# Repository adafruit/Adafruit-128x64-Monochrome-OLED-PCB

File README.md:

## Adafruit 128x64 Monochrome OLED PCB
<a href="http://www.adafruit.com/products/326"><br/>
<a href="http://www.adafruit.com/products/326"><br/>
Click here to purchase one from the Adafruit shop</a>

These displays are small, only about 1" diagonal, but very readable due to the high contrast of an OLED display. This display is made of 128x64 individual white OLED pixels, each one is turned on or off by the controller chip. Because the display makes its own light, no backlight is required. This reduces the power required to run the OLED and is why the display has such high contrast; we really like this miniature display for its crispness!

This breakout can be used with either an SPI or I2C interface - selectable by soldering two jumpers on the back. The design is completely 5V-ready, with an onboard regulator and built in boost converter. It's easier than ever to connect directly to your 3V or 5V microcontroller without needing any kind of level shifter!

This is the PCB for the Adafruit 128x64 I2C/SPI/Parallel OLED breakout board. The format is EagleCAD schematic and board layout
- http://www.adafruit.com/products/326

### License

Adafruit invests time and resources providing this open source design, please support Adafruit and open-source hardware by purchasing products from [Adafruit](https://www.adafruit.com)!

All text above must be included in any redistribution

Designed by Limor Fried/Ladyada for Adafruit Industries.
Creative Commons Attribution/Share-Alike, all text above must be included in any redistribution. 
See license.txt for additional information.

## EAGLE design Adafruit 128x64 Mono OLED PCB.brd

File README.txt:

This is the PCB for the Adafruit 128x64 I2C/SPI/Parallel OLED breakout board
Format is EagleCAD schematic and board layout

For more details, check out the product page at

-----> http://www.adafruit.com/products/326

Adafruit invests time and resources providing this open source design, 
please support Adafruit and open-source hardware by purchasing 
products from Adafruit!

Designed by Adafruit Industries.  
Creative Commons Attribution, Share-Alike license, check license.txt for more information
All text above must be included in any redistribution

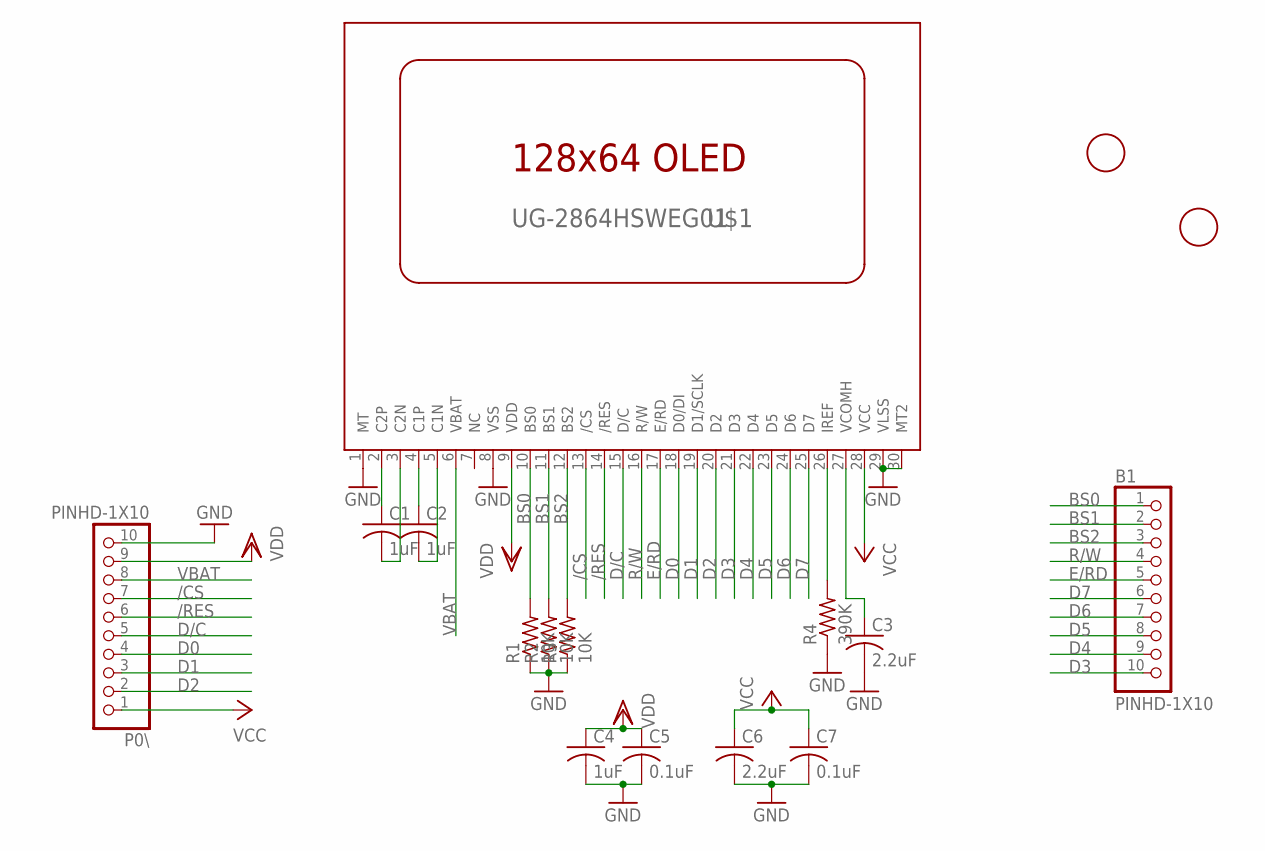
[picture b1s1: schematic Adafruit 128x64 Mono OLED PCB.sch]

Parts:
B1: PINHD-1X10; 1X10-BIG
C1, C2, C4: 1uF; C0805K
C3, C6: 2.2uF; C0805K
C5, C7: 0.1uF; C0805K
P0\: PINHD-1X10; 1X10-BIG
R1, R2, R3: 10K; R0805
R4: 390K; R0805
U$1: UG-2864HSWEG01; 1X30-0.7MM
U$3, U$4: FIDUCIAL; FIDUCIAL_1MM

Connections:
/CS: P0\.7, U$1.13 (/CS)
/RES: P0\.6, U$1.14 (/RES)
BS0: B1.1, R1.2, U$1.10 (BS0)
BS1: B1.2, R2.2, U$1.11 (BS1)
BS2: B1.3, R3.2, U$1.12 (BS2)
D0: P0\.4, U$1.18 (D0/DI)
D1: P0\.3, U$1.19 (D1/SCLK)
D2: P0\.2, U$1.20 (D2)
D3: B1.10, U$1.21 (D3)
D4: B1.9, U$1.22 (D4)
D5: B1.8, U$1.23 (D5)
D6: B1.7, U$1.24 (D6)
D7: B1.6, U$1.25 (D7)
D/C: P0\.5, U$1.15 (D/C)
E/RD: B1.5, U$1.17 (E/RD)
GND: C3.2, C4.2, C5.2, C6.2, C7.2, P0\.10, R1.1, R2.1, R3.1, R4.1, U$1.1 (MT), U$1.8 (VSS), U$1.29 (VLSS), U$1.30 (MT2)
unnamed: C1.2, U$1.3 (C2N)
unnamed: C1.1, U$1.2 (C2P)
unnamed: C2.1, U$1.4 (C1P)
unnamed: C2.2, U$1.5 (C1N)
unnamed: R4.2, U$1.26 (IREF)
unnamed: C3.1, U$1.27 (VCOMH)
R/W: B1.4, U$1.16 (R/W)
VBAT: P0\.8, U$1.6 (VBAT)
VCC: C6.1, C7.1, P0\.1, U$1.28 (VCC)
VDD: C4.1, C5.1, P0\.9, U$1.9 (VDD)

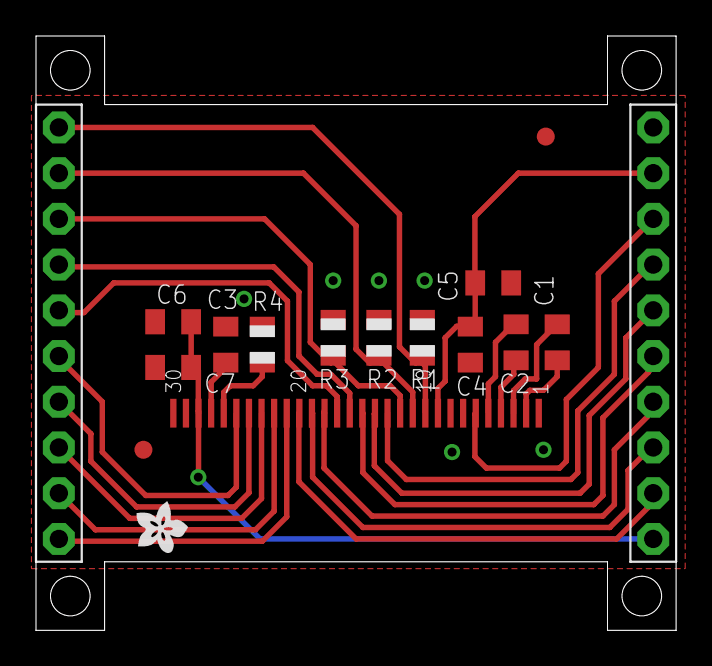
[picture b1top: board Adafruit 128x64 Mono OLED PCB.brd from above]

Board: 2 copper layers, 35.6 x 33.0 mm, 17 parts (0 on the bottom side), 26 nets.

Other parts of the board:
U$2: ADAFRUIT200MIL

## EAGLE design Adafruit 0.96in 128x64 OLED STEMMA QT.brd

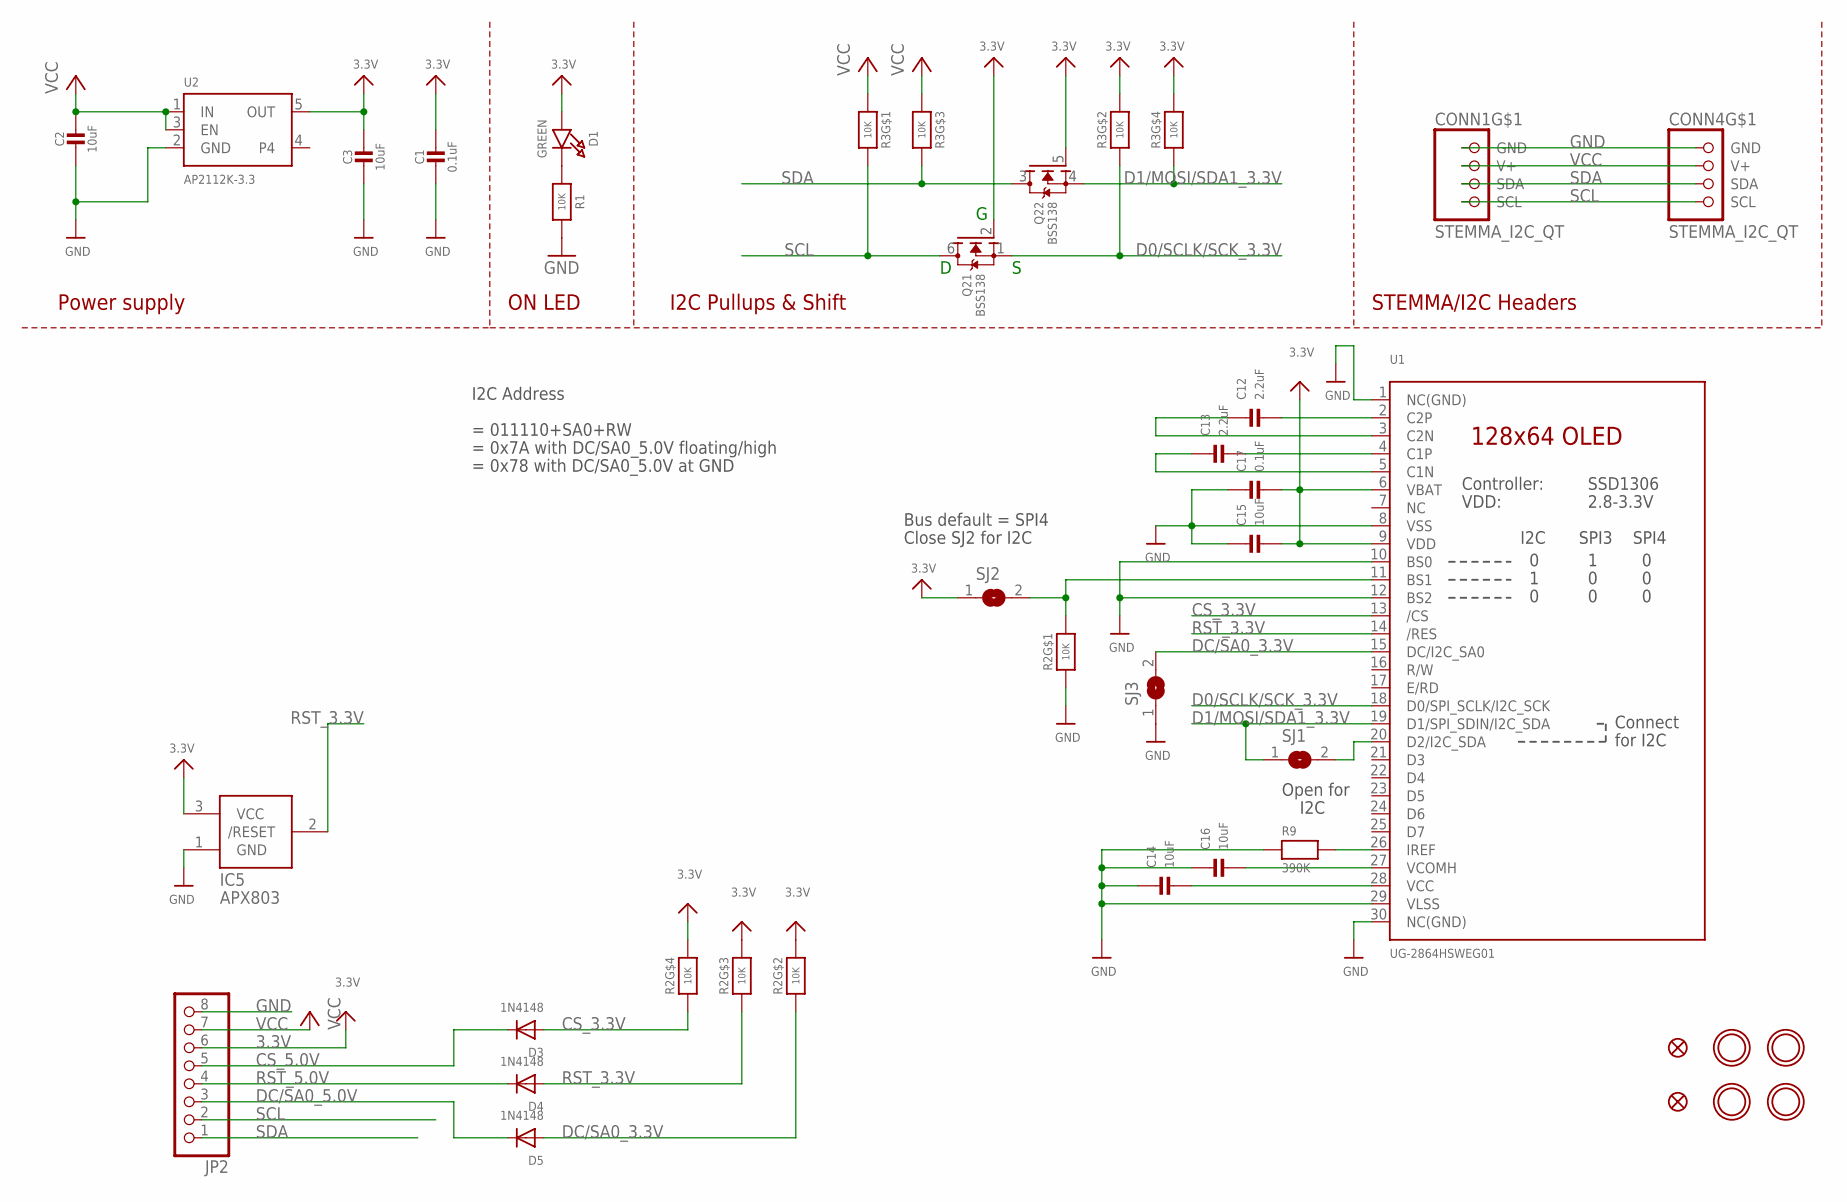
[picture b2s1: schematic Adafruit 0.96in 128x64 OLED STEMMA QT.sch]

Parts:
C1, C17: 0.1uF; 0603-NO
C2, C3, C14, C15, C16: 10uF; 0805-NO
C12, C13: 2.2uF; 0805-NO
CONN1, CONN4: STEMMA_I2C_QT; JST_SH4
D1: GREEN; CHIPLED_0603_NOOUTLINE
D3, D4, D5: 1N4148; SOD-323
FID3, FID4: FIDUCIAL_1MM
IC5: APX803; SOT23
JP2: HEADER-1X870MIL; 1X08_ROUND_70
Q2: BSS138; SOT363
R1: 10K; 0603-NO
R2, R3: 10K; RESPACK_4X0603
R9: 390K; 0603-NO
SJ1, SJ2: SOLDERJUMPERCLOSED; SOLDERJUMPER_CLOSEDWIRE
SJ3: SOLDERJUMPER; SOLDERJUMPER_ARROW_NOPASTE
U1: UG-2864HSWEG01; UG-2864HSWEG01_0.96IN_WRAPAROUND
U2: AP2112K-3.3; SOT23-5
U$1, U$17, U$19, U$21: MOUNTINGHOLE2.5; MOUNTINGHOLE_2.5_PLATED

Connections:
3.3V: C1.1, C3.1, C15.2, C17.2, D1.A, IC5.3 (VCC), JP2.6, Q2.2 (G), Q2.5 (G), R2.5 (2), R2.6 (2), R2.7 (2), R3.2 (1), R3.4 (1), SJ2.1, U1.6 (VBAT), U1.9 (VDD), U2.5 (OUT)
CS_3.3V: D3.A, R2.4 (1), U1.13 (/CS)
CS_5.0V: D3.C, JP2.5
D0/SCLK/SCK_3.3V: Q2.1 (S), R3.7 (2), U1.18 (D0/SPI_SCLK/I2C_SCK)
D1/MOSI/SDA1_3.3V: Q2.4 (S), R3.5 (2), SJ1.1, U1.19 (D1/SPI_SDIN/I2C_SDA)
DC/SA0_3.3V: D5.A, R2.2 (1), SJ3.2, U1.15 (DC/I2C_SA0)
DC/SA0_5.0V: D5.C, JP2.3
GND: C1.2, C2.2, C3.2, C14.1, C15.1, C16.1, C17.1, CONN1.1 (GND), CONN4.1 (GND), IC5.1 (GND), JP2.8, R1.2, R2.1, R9.1, SJ3.1, U1.1 (NC(GND)), U1.8 (VSS), U1.10 (BS0), U1.12 (BS2), U1.29 (VLSS), U1.30 (NC(GND)), U2.2 (GND)
unnamed: D1.C, R1.1
unnamed: R2.8 (2), SJ2.2, U1.11 (BS1)
unnamed: R9.2, U1.26 (IREF)
unnamed: C12.2, U1.2 (C2P)
unnamed: C12.1, U1.3 (C2N)
unnamed: C13.2, U1.4 (C1P)
unnamed: C13.1, U1.5 (C1N)
unnamed: C14.2, U1.28 (VCC)
unnamed: C16.2, U1.27 (VCOMH)
unnamed: SJ1.2, U1.20 (D2/I2C_SDA)
RST_3.3V: D4.A, IC5.2 (/RESET), R2.3 (1), U1.14 (/RES)
RST_5.0V: D4.C, JP2.4
SCL: CONN1.4 (SCL), CONN4.4 (SCL), JP2.2, Q2.6 (D), R3.8 (2)
SDA: CONN1.3 (SDA), CONN4.3 (SDA), JP2.1, Q2.3 (D), R3.6 (2)
VCC: C2.1, CONN1.2 (V+), CONN4.2 (V+), JP2.7, R3.1, R3.3 (1), U2.1 (IN), U2.3 (EN)

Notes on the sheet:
I2C Pullups & Shift
STEMMA/I2C Headers
ON LED
Power supply
Bus default = SPI4
Close SJ2 for I2C
= 011110+SA0+RW
= 0x7A with DC/SA0_5.0V floating/high
= 0x78 with DC/SA0_5.0V at GND
I2C Address
Open for
I2C

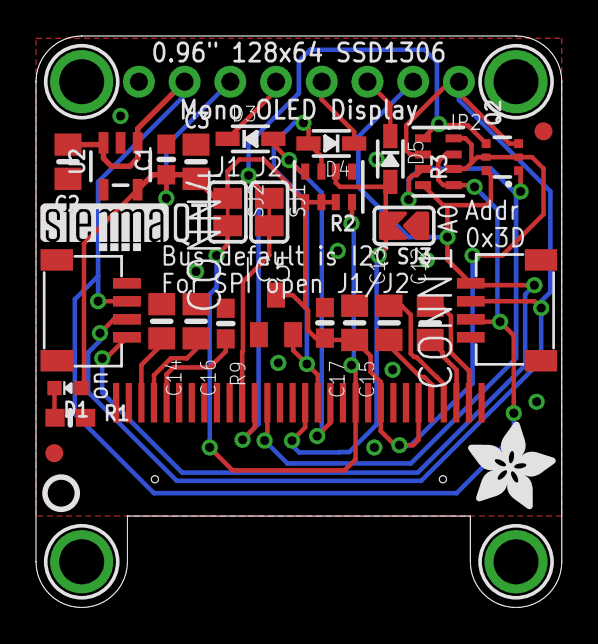
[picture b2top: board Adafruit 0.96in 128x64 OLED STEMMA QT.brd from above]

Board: 2 copper layers, 29.2 x 31.8 mm, 36 parts (1 on the bottom side), 23 nets.

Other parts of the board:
U$8: ADAFRUIT_5MM
U$25: PCBFEAT-REV-040
U$31: STEMMAQT

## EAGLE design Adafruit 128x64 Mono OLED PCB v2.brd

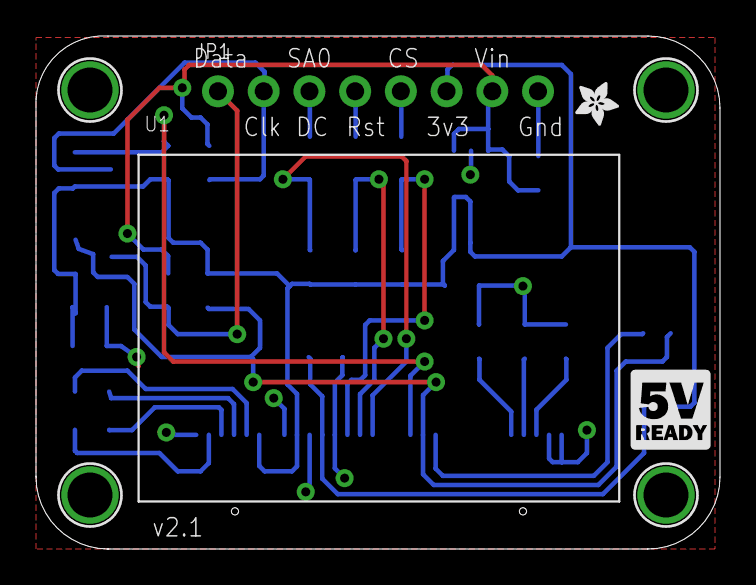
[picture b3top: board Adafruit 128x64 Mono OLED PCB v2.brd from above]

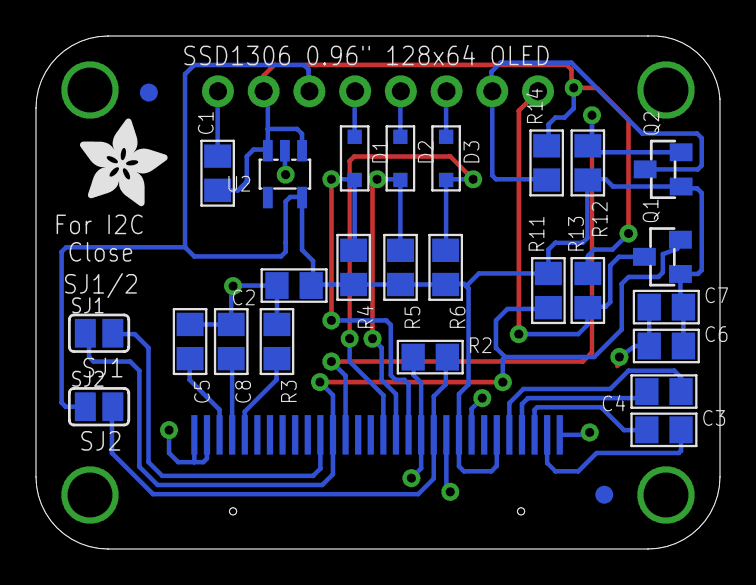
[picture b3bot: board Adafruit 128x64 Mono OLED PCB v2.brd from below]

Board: 2 copper layers, 38.0 x 28.5 mm, 36 parts (28 on the bottom side), 22 nets.

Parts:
C1, C2, C5: 10uF; 0805
C3, C4, C6, C7: 1uF; 0805
C8: 2.2uF/16V; 0805
D1, D2, D3: 1N4148; SOD-323
FID1, FID2: FIDUCIAL""; FIDUCIAL_1MM
JP1: 1X08_ROUND_70
Q1, Q2: BSS138; SOT23-WIDE
R2, R4, R5, R6, R11, R12, R13, R14: 10K; 0805
R3: 390K; 0805
SJ1, SJ2: SOLDERJUMPER_REFLOW_NOPASTE
U1: UG-2864HSWEG01; UG-2864HSWEG01_0.96IN_WRAPAROUND
U2: SOT23-5
U$3: ADAFRUIT_5MM
U$23, U$24, U$25, U$26: MOUNTINGHOLE2.5; MOUNTINGHOLE_2.5_PLATED
U$27: ADAFRUIT_2.5MM
U$28: LOGIC_5VREADY_5MM

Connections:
3.3V: C2.1, C6.2, C7.2, JP1.6, Q1.1, Q2.1, R4.2, R5.2, R6.2, R11.2, R12.2, SJ2.1, U1.6, U1.9, U2.5
CS_3.3V: D1.A, R4.1, U1.13
CS_5.0V: D1.C, JP1.5
D0/SCLK/SCK_3.3V: Q2.2, R12.1, U1.18
D0/SCLK/SCK_5.0V: JP1.2, Q2.3, R14.1
D1/MOSI/SDA1_3.3V: Q1.2, R11.1, SJ1.1, U1.19
D1/MOSI/SDA_5.0V: JP1.1, Q1.3, R13.1
DC/SA0_3.3V: D3.A, R6.1, U1.15
DC/SA0_5.0V: D3.C, JP1.3
GND: C1.2, C2.2, C5.1, C6.1, C7.1, C8.1, JP1.8, R2.1, R3.1, U1.1, U1.8, U1.10, U1.12, U1.29, U1.30, U2.2
unnamed: R2.2, SJ2.2, U1.11
unnamed: SJ1.2, U1.20
unnamed: R3.2, U1.26
unnamed: C3.2, U1.2
unnamed: C3.1, U1.3
unnamed: C4.2, U1.4
unnamed: C4.1, U1.5
unnamed: C5.2, U1.28
unnamed: C8.2, U1.27
RST_3.3V: D2.A, R5.1, U1.14
RST_5.0V: D2.C, JP1.4
VIN: C1.1, JP1.7, R13.2, R14.2, U2.1, U2.3

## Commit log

2011-08-12 Board & schem files for 128x64 oled
2012-03-08 rename!
2012-03-08 read
2016-07-24 Dimension information for 128x64 Mono OLED PCB
2020-08-06 Adding updated board files.
2020-08-06 Add image asset.
2020-08-06 Add updated image.
2026-06-03 update file format to XML

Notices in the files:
parts and their libraries:
microbuilder: This work is placed in the public domain, and may be freely used for commercial and non-commercial work with the following conditions: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
